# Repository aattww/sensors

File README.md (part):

# Summary

This project consists of simple Atmel ATmega328P based nodes utilizing HopeRF LoRa RFM95W/RFM96W radios. Battery-powered nodes measure temperature, humidity and barometric pressure, depending on connected hardware. Externally powered pulse type nodes count pulses from different utility meters and also connect to Kamstrup Multical energy meters. Gateway receives and collects these measurements from the sensor nodes and can be accessed by serial communication using Modbus RTU protocol via either two-wire RS-485 or common 3.3 volt UART. This enables interfacing with many DIY home automation systems such as [Domoticz](https://www.domoticz.com/), [Home Assistant](https://www.home-assistant.io/) and [openHAB](https://www.openhab.org/). Sensors uses custom circuit boards but is programmed with Arduino IDE.

This project is a complete package: it includes both hardware designs and software. *Schematics* contains PCB designs so you can manufacture or order PCBs from a factory and solder the nodes. Software is ready to be uploaded as it is. If you do not want to use the hardware designs provided, you should be able to use, for example, Arduino Pro Minis with protoboards instead. Browse through the .inos and the schematics to find out pin definitions. Remember to take into account battery usage if using Pro Minis or other "full size" Arduinos. Also remember that the components used are mostly 3.3 volt tolerant only, so using a 5 volt Uno requires level shifting.

Skip directly to [Instructions](#instructions), although I strongly recommend reading the whole readme first.

# Table of Contents

* [External requirements](#external-requirements)
  * [Libraries](#libraries)
  * [Hardware package (core)](#hardware-package-core)
* [Gateway](#gateway)
  * [Modbus registers](#modbus-registers)
    * [Gateway specific registers](#gateway-specific-registers)
    * [Battery powered node specific registers](#battery-powered-node-specific-registers)
    * [Pulse node specific registers](#pulse-node-specific-registers)
    * [Pulse node with Kamstrup Multical 602 energy meter specific registers](#pulse-node-with-kamstrup-multical-602-energy-meter-specific-registers)
* [Node types](#node-types)
  * [Battery](#battery)
    * [Supported sensors](#supported-sensors)
  * [Pulse](#pulse)
  * [Pulse with Kamstrup Multical 602 energy meter](#pulse-with-kamstrup-multical-602-energy-meter)
* [Radios](#radios)
* [Schematics and PCB](#schematics-and-pcb)
  * [BOM](#bom)
    * [Gateway / Pulse / Pulse with Kamstrup Multical](#gateway--pulse--pulse-with-kamstrup-multical)
    * [Battery](#battery-1)
  * [LEDs](#leds)
    * [Gateway](#gateway-1)
    * [Battery](#battery-2)
    * [Pulse / Pulse with Kamstrup Multical](#pulse--pulse-with-kamstrup-multical)
  * [Headers, terminals and buttons](#headers-terminals-and-buttons)
    * [Gateway](#gateway-2)
    * [Battery](#battery-3)
    * [Pulse / Pulse with Kamstrup Multical](#pulse--pulse-with-kamstrup-multical-1)
* [Instructions](#instructions)
* [Version history](#version-history)

# External requirements

Sensors requires a few external components to work: libraries provide functions for radio communications and connected sensors while hardware package handles needed fuses to work with custom boards used by Sensors. Follow carefully especially the instructions regarding RadioHead and Cryptography libraries, as these require a couple of underlying changes.

## Libraries

**RadioHead Packet Radio library for embedded microprocessors** provides support for RFM95W/RFM96W radios (and many others as well). Download from [airspayce.com](https://www.airspayce.com/mikem/arduino/RadioHead/). After extracting the library to your Arduino IDE libraries folder you will have to do one adjustment. In the beginning of *RadioHead/RH_RF95.h* change line  
`#define RH_RF95_FIFO_SIZE 255`  
to  
`#define RH_RF95_FIFO_SIZE 64`  
Communication will not work without this change. You also risk running out of SRAM without this adjustment.

**Arduino Cryptography Library** includes support for encryption. If you do not plan to encrypt traffic, you will not need this library. Download from [github.com](https://github.com/rweather/arduinolibs). You will need to download the ZIP and extract contents of *libraries* to your Arduino IDE libraries folder. Also remember to uncomment the following line at the very end of *RadioHead/RadioHead.h* to enable encryption:  
`//#define RH_ENABLE_ENCRYPTION_MODULE`  
You will also need to disable watchdog entropy harvesting by commenting out the following line at the beginning of *Crypto/RNG.cpp* because watchdog timer is already used by battery powered nodes:  
`#define RNG_WATCHDOG 1      // Harvest entropy from watchdog jitter.`  
If you are overwhelmed by all this, you may just want not to enable encryption at all. After all, Sensors is not exactly high security system anyway.

**LowPowerLab SI7021** library is needed to work with Silicon Labs Si7021 temperature and humidity sensor. Download from [github.com](https://github.com/LowPowerLab/SI7021).

**SparkFun BME280 Arduino Library** interfaces with Bosch Sensortech BME280 temperature, humidity and barometric pressure sensor. Documentation at [github.com](https://github.com/sparkfun/SparkFun_BME280_Arduino_Library). Install using Arduino IDE Library Manager.

## Hardware package (core)

Sensors uses a bit different hardware design than regular Arduino boards. For example, battery operated nodes run on internal 1 MHz clock and gateway uses external 8 MHz crystal. They also lack bootloader (although you could use it, hardware just doesn't provide serial pins to burn new firmware using bootloader anyway). Instead, program is flashed using ICSP through ISP header.

You could set the necessary fuses manually but it is considerably easier to just use a ready-made hardware package. MCUdude has a nice core specifically to do this. Download MCUdude's MiniCore from [github.com](https://github.com/MCUdude/MiniCore).

# Gateway

Gateway collects data from nodes and acts as an relay to a [Modbus](https://en.wikipedia.org/wiki/Modbus) network. By using Maxim Integrated MAX3485 RS-485 transceiver gateway can be connected to an existing RS-485 Modbus RTU network as a slave. Omitting the transceiver provides a direct TTL serial port. This can be accessed with, for example, another Arduino board, FTDI chip or connected directly to a Raspberry Pi. Regardless of the physical connection, gateway is accessed using Modbus protocol. Gateway requires regulated 3.3 volts or (unregulated) 5-12 volts DC power supply. In addition, gateway has three pulse inputs (pulse values are periodically saved to EEPROM and restored on power-up), one of which can be used as an NTC thermistor input. These inputs are also accessible via Modbus.

One drawback of Modbus protocol is that a slave can not inform the master of new messages. For this, pulse 2 can be enabled to work as an external interrupt. This pin behaves like an emulated open collector output (external high state voltage is limited to 3.3 volts, however). The pin will be pulled to ground when a message is received either from an *important* node or any node, depending on the gateway settings. After Modbus read has been done, this pin will be set back to high impedance state.

**Warning:** UART serial port is 3.3 volts, so don't connect it to a 5 volt system.

Why Modbus? Modbus is an easy to use and integrate protocol for this kind of data transfer. Although it is old and somewhat limited in features, it still provides all the necessary things and is widely used in industry. Libraries to access it exist for more or less every platform. Also, most DIY home automation systems ([Home Assistant](https://www.home-assistant.io/), [Domoticz](https://www.domoticz.com/) and [openHAB](https://www.openhab.org/) to name a few) have Modbus support.

## Modbus registers

Registers can be accessed using either function code 3 (read holding registers) or 4 (read input registers). Both return the same register values. Note that registers not defined can not be read. For example, trying to read registers 21-99 or 108-199 will return *illegal data address exception*.

### Gateway specific registers

| Address | Number | Name | Type / Unit | Notes |
| ------- | ------ | ---- | ---- | ----- |
| 0       | 30001  | Modbus errors (CRC failed or corrupted) | Counter |  |
| 1       | 30002  | Modbus overflown frames | Counter |  |
| 2       | 30003  | Modbus illegal function reads | Counter |  |
| 3       | 30004  | Modbus illegal address reads | Counter |  |
| 4       | 30005 | Modbus frames received | Counter |  |
| 5       | 30006  | Modbus frames sent | Counter |  |
| 6       | 30007  | Nodes during last hour | Counter |  |
| 7       | 30008  | Nodes during last 12 hours | Counter |  |
| 8       | 30009  | Nodes during last 24 hours | Counter |  |
| 9       | 30010  | At least one node low on battery | Boolean |  |
| 10       | 30011  | Gateway out of memory | Boolean |  |
| 11       | 30012  | Gateway uptime | Hour | |
| 12       | 30013  | Firmware version | | 8 MSB = major, 8 LSB = minor |
| 13       | 30014  | Status |  | See below for bits. |
| 14       | 30015  | Pulse 1 | Counter | 32 bit |
| 16       | 30017  | Pulse 2 | Counter | 32 bit |
| 18       | 30019  | Pulse 3 / Temperature | Counter / °C | 32 bit |
| 20       | 30021  | Last received node ID |  |  |

Status register bits (from LSB to MSB):
* Bit 0 **External SRAM:** *1* if gateway has external SRAM, *0* if using internal SRAM. Affects maximum number of nodes, see notes in [Schematics and PCB](#schematics-and-pcb).
* Bit 1-15 **Reserved**

### Battery powered node specific registers

First address is *node id * 100*. For example, this table shows addresses for a node id 1. Similarly, measurements for node id 2 start at address 200, and so on.

| Address | Number | Name | Type / Unit | Notes |
| ------- | ------ | ---- | ---- | ----- |
| 100       | 30101  | Last received | Minute | When was node last seen. |
| 101       | 30102  | Battery voltage | mV | Current battery voltage. |
| 102       | 30103  | Transmit power | % | Relative transmit power. |
| 103       | 30104  | Transmit interval | Minute | How often the node transmits at least. |
| 104       | 30105  | Header |  | Only 8 LSB, debug data. See below for bits. |
| 105       | 30106  | Temperature | °C | ×10 |
| 106       | 30107  | Relative humidity | RH% | ×10. **Only if node has Si7021 or BME280.** |
| 107       | 30108  | Barometric pressure / Temperature | hPa / °C | ×10. **Pressure if node has BME280, temperature if node has both Si7021 and NTC.** |

Header register bits (from LSB to MSB):
* Bit 0-2 **Node type:** Internal definiton of the node type.
* Bit 3 **Reserved**
* Bit 4 **Battery-powered:** *1* if node is battery-powered, *0* if powered externally.
* Bit 5 **Important:** *1* if node has declared itself important, *0* if not.
* Bit 6-7 **Reserved**

### Pulse node specific registers

First address is *node id * 100*. For example, this table shows addresses for a node id 2. Similarly, measurements for node id 3 start at address 300, and so on.

| Address | Number | Name | Type / Unit | Notes |
| ------- | ------ | ---- | ---- | ----- |
| 200       | 30201  | Last received | Minute | When was node last seen. |
| 201       | 30202  | Transmit power | % | Relative transmit power. |
| 202       | 30203  | Transmit interval | Minute | How often the node transmits at least. |
| 203       | 30204  | Header |  | Only 8 LSB, debug data. See below for bits. |
| 204       | 30205  | Pulse 1 | Counter | 32 bit |
| 206       | 30207  | Pulse 2 | Counter | 32 bit |
| 208       | 30209  | Pulse 3 / Temperature | Counter / °C | 32 bit |

Header register bits (from LSB to MSB):
* Bit 0-2 **Node type:** Internal definiton of the node type.
* Bit 3 **Reserved**
* Bit 4 **Battery-powered:** *1* if node is battery-powered, *0* if powered externally.
* Bit 5 **Important:** *1* if node has declared itself important, *0* if not.
* Bit 6-7 **Reserved**

### Pulse node with Kamstrup Multical 602 energy meter specific registers

First address is *node id * 100*. For example, this table shows addresses for a node id 3. Similarly, measurements for node id 4 start at address 400, and so on.

| Address | Number | Name | Type / Unit | Notes |
| ------- | ------ | ---- | ---- | ----- |
| 300       | 30301  | Last received | Minute | When was node last seen. |
| 301       | 30302  | Transmit power | % | Relative transmit power. |
| 302       | 30303  | Transmit interval | Minute | How often the node transmits at least. |
| 303       | 30304  | Header |  | Only 8 LSB, debug data. See below for bits. |
| 304       | 30305  | Pulse 1 | Counter | 32 bit |
| 306       | 30307  | Pulse 2 | Counter | 32 bit |
| 308       | 30309  | Pulse 3 / Temperature | Counter / °C | 32 bit |
| 310       | 30311  | Heat energy | kWh | 32 bit |
| 312       | 30313  | Actual flow | l/h | 32 bit |
| 314       | 30315  | Volume | m³ | ×100. 32 bit |
| 316       | 30317  | Actual power | kW | ×10. 32 bit |
| 318       | 30319  | Actual t₁ | °C | ×100. 32 bit |
| 320       | 30321  | Actual t₂ | °C | ×100. 32 bit |

Header register bits (from LSB to MSB):
* Bit 0-2 **Node type:** Internal definiton of the node type.
* Bit 3 **Reserved**
* Bit 4 **Battery-powered:** *1* if node is battery-powered, *0* if powered externally.
* Bit 5 **Important:** *1* if node has declared itself important, *0* if not.
* Bit 6-7 **Reserved**

# Node types

Sensors includes two main types of nodes: battery and pulse. Battery-powered low-power nodes monitor temperature, humidity and pressure. Pulse type nodes are externally powered and count pulses from utility meters. Pulse nodes also support connecting one NTC thermistor for temperature monitoring and RS-485 Modbus RTU. The latter enables the node to be connected to a Kamstrup Multical 602 energy meter.

## Battery

Battery powered sensors provide simple nodes to monitor temperature, humidity and barometric pressure. These nodes operate on two normal 1.5 volt AA alkaline batteries. If longer lifetime is needed or if node is placed in cold environment, more expensive 1.5 volt AA-size lithium batteries can also be used.

**Warning:** Hardware provides no reverse voltage protection in order to conserve power and to keep number of parts minimal, so **make sure to observe polarity when inserting batteries or you will destroy the node**.

Nodes spend most of the time sleeping, only to wake up to take measurements and send values to gateway. Frequency can be controlled through settings at the beginning of the code file. In threshold mode, nodes wake up periodically and take measurements. If values differ enough from previously sent ones, a message is sent. If not, nodes return to sleep. However, there is a specific force time controlling how often a new message is sent at least regardless of threshold. If a node is not operating in threshold mode, it will send a message every time it wakes up.

### Supported sensors

Nodes support three types of sensors: Silicon Labs Si7021, Bosch Sensortech BME280, and a common NTC thermistor. The first one has temperature and humidity, the second one adds barometric pressure, and the latter provides only temperature. A node can have only one kind of sensor, or as a special case both Si7021 and NTC at the same time. PCB provides footprints for all, and the exact type is defined in runtime. That is, every node is flashed with the same software and it checks at bootup what kind of sensor configuration is connected.

**Si7021** sensors can be bought as breakout boards from eBay and similar places for a couple of dollars. When buying the sensor, get one that does not include voltage regulator and I2C level shifting. Battery powered nodes operate on 3.3 volts so Si7021 can be fed directly. Not having (unnecessary) regulator saves battery power. For example, [this one](https://www.ebay.com/itm/SMD-MINI-Si7021-Temperature-and-Humidity-Sensor-I2C-Interface-for-Arduino/264394330907) is recommended, while [this one](https://www.ebay.com/itm/Si7021-Industrial-High-Precision-Humidity-Sensor-I2C-Interface-for-Arduino/201539848414) is not.

**BME280** sensors are also available in eBay, Aliexpress and similar as breakout boards. They are a bit more expensive. These seem not to be available without the onboard regulator, so if you want to lower power consumption, your only option is to remove the regulator. Example image of a removed regulator [shown here](images/bme280.jpg). [This sensor](https://www.ebay.com/itm/Breakout-Temperature-Humidity-Barometric-Pressure-BME280-Digital-Sensor-Module/401000227934), for example, has been used successfully.

**Note:** Chinese sellers sometimes mix the BME280 with earlier and less featured BMP280. Be careful when buying the sensor. Info about this for example [here](https://goughlui.com/2018/08/05/note-bosch-sensortec-bmp280-vs-bme280-sensor-confusion/) and [here](https://www.meteocercal.info/forum/Thread-Bosch-Sensortec-BMP280-vs-BME280-Sensor-Confusion).

**NTC thermistors** can be purchased from the same places as the other sensors. When buying thermistors, make sure you get three necessary values: *nominal resistance*, *nominal temperature* and *beta coefficient*. For example, [this thermistor](https://www.ebay.com/itm/5PCS-1m-NTC-Thermistor-accuracy-temperature-sensor-10K-1-3950-Waterproof-Probe/311572298670) has been successfully used and works with the default values.

## Pulse

Pulse type nodes are intended to measure pulses from a water, electricity, gas or other kind of meter with pulse output. Nodes have three pulse inputs, one of which can be used as an NTC thermistor input instead of a pulse input. Pulse inputs are pulled high internally by microcontroller or with optional external resistors, and connected meter pulls it low to ground. Pulse values are periodically saved to EEPROM and restored on power-up. Pulse nodes require either regulated 3.3 volts or (unregulated) 5-12 volts DC power supply. They use the same PCB as the gateway.

## Pulse with Kamstrup Multical 602 energy meter

These nodes are regular pulse nodes with added support for Kamstrup Multical 602 energy meter. Node is connected by RS-485 to a Multical 602 energy meter and periodically reads certain values from the meter. See Modbus register listing above for these values.

**Note:** Multical 602 seems to be discontinued and replaced by Multical 603. According to datasheet, Multical 603 supports the same Modbus registers as the old 602. Therefore nodes should work with newer 603s but this is untested.

**Protip:** Using this node as an example, it should be quite easy to connect some other kind of Modbus RTU capable device to a Pulse type node and adjust code accordingly. This way you can read any other Modbus meters or devices via Sensors nodes.

# Radios

Sensors utilize HopeRF RFM95W and RFM96W LoRa radios. RFM95W is for 868/915 MHz and RFM96W for 433 MHz. These are cheap low power radios with very good range. Battery nodes use wire or helical antennas, while gateway and pulse nodes have SMA connectors for better performing antennas. Please consider local regulations when choosing frequency range, bandwidth, transmit power and other radio related settings. Nodes automatically adjust transmit power to the lowest possible level.

Attainable range depends greatly on numerous things but personally I have easily achieved over one kilometer through a reinforced concrete wall and a metal facade. This was between a gateway with a dipole SMA antenna and a battery node with helical antenna. The same setup also reached over 200 meters through buildings in a more built environment. However, as with wireless communication in general, your results will vary.

**Note:** On the PCB there is footprint for older HopeRF RFM69HW radio as well. It should work, but it has not been tested and there is currently no support in software for this. Feel free to create a new branch and implement it.

# Schematics and PCB

Following is the table of bill of materials. Not all components are needed, see the notes below for these parts. Majority of the SMD components are 1206 package for easier hand soldering. Gateways and pulse nodes share the same PCB.

Some notes:
* MAX3485 transceiver is needed only if you connect the gateway to an existing RS-485 network. If you use direct UART it is not needed. In this case, remember to also short *COMM_JMP* at the bottom.
* External pull-up resistors are probably not needed in most cases as internal ones in ATmega328P are usually adequate. However, if you are connecting NTC thermistor to pulse 3, remember to solder the 10 kOhm series resistor.
* Pulse smoothing capacitors are optional. Use them if you encounter erroneous pulses, ie. too many pulses are counted. For example, I had a [rain gauge](https://www.amazon.co.uk/dp/B00QDMBXUA) connected to a pulse input with a rather long cable (about 10 meters running next to mains power supply for part of length). Extra pulses were counted even when no rain had fallen. Adding a 10 uF capacitor removed these wrong measures.
* MIC5209 regulator makes it possible to power the gateway/pulse node with DC voltage between 5-12 volts (technically up to 16 volts but it might start to get warm). If you can supply the board with regulated 3.3 volts, you can omit the regulator. In this case, also short the *PWR_JMP*.
* The Microchip 23K256 SRAM chip is optional. Without it, gateway falls back using its internal SRAM. However, this severely limits the amount of nodes. With the 23K256 gateway supports 100 nodes regardless of type, without it only 10. This varies by node type, however. For example, without external SRAM gateway supports 10 battery nodes, or 5 pulse nodes, or 6 battery nodes plus 2 pulse nodes.
* SMA connector can be omitted and replaced with a wire or a helical antenna if these smaller gain antennas are sufficient. You can also, with some very careful alignment, solder a u.FL connector on to the SMA connector footprint. This allows using a u.FL to SMA pigtail to move the actual SMA connector away.

I have successfully ordered PCBs from Seeed Studio. You can get boards for 10 gateways/pulse nodes and 10 battery nodes for $9.80 plus postage. Of course any prototype PCB factory will work. PCBs are designed not to have any tight spacings or need for strict tolerances. For gateway and pulse node, select 1.6mm thickness (the enclosure will hold the PCB better). With battery nodes, boards can be thinner (for example 1.2mm works well). Other options should be okay with defaults.

Boards are designed to fit the enclosures mentioned in the table. [Bud Industries DMB-4771](https://www.budind.com/view/Plastic+Boxes/DIN+Rail+Mount+Multi-Board+Box) is a 35mm DIN rail mounted box, while [Supertronic PP42](http://www.supertronic.com/en/cajas_de_plastico/sensors/29/pp42/50) is a simple wall mounted enclosure (use double-sided tape). In the *schematics* folder there is also *AP9_holder.stl* which is a 3D model of a simple holder to fix a battery node into an [ABB AP9 junction box](https://new.abb.com/products/2TKA140012G1/ap9-junction-box-ip65). This is especially handy if you install a node outside and have access to a 3D printer. You will need two holders and a set of small screws. You will also need to have a way to make the box rain-proof but still let humidity and temperature in. Poking some holes into membrane cable entries is one way, or if you want to go professional, use a sintered protective cover. [This](https://www.ebay.com/itm/Protective-Cover-SHT10-SHT20-Soil-Temperature-Humidity-Moisture-Sensor-Shell/173940209491) has been proven to work: a BME280 breakout board will *just* fit inside if you solder wires to the board as [shown here](images/bme280.jpg). Remember to wrap the breakout board (but not the sensor itself) with some insulating tape or use heat shrink to prevent short circuits. [This image](images/si7021_wired.jpg) shows an Si7021 breakout board prepared for outdoor sensor use. You will also need to drill off the plastic inside with the connectors of the protective cover. Use some imagination here. A ready-made weatherproofed sensor looks something like [this](images/weatherproof_node.jpg). Connecting an NTC thermistor with sufficiently long wire will make a nice water temperature node as shown [here](images/water_temperature_node.jpg).

## BOM

### Gateway / Pulse / Pulse with Kamstrup Multical

| Part | Value | Device | Package | Type | Notes |
| ---- | ----- | ------ | ------- | ---- | ----- |
| C1 | 100 nF | Decoupling capacitor | 1206 | Ceramic | |
| C2 | 22 pF | Crystal capacitor | 1206 | Ceramic | |
| C3 | 22 pF | Crystal capacitor | 1206 | Ceramic | |
| C4 | 100 nF | Decoupling capacitor | 1206 | Ceramic | Used only with RFM95W / RFM96W. |
| C5 | 100 nF | Decoupling capacitor | 1206 | Ceramic | Used only with RFM69HW. |
| C6 | 100 nF | Decoupling capacitor | 1206 | Ceramic | Used only with U2 (MAX3485). |
| C7 | 1 uF | Power input capacitor | 1206 | Tantalum | |
| C8 | 1 uF | Power output capacitor | 1206 | Tantalum | |
| C9 | 10 uF | Power output capacitor | 1206 | Ceramic | |
| C10 | 100 nF | Decoupling capacitor | 1206 | Ceramic | Used only with 23K256. |
| C11 | Depends | Pulse 3 smoothing capacitor | 1206 | Ceramic | Use if erroneous pulses are counted. |
| C12 | Depends | Pulse 2 smoothing capacitor | 1206 | Ceramic | Use if erroneous pulses are counted. |
| C13 | Depends | Pulse 1 smoothing capacitor | 1206 | Ceramic | Use if erroneous pulses are counted. |
| R1 | 10 kOhm | Reset pull-up resistor | 1206 | | |
| R2 | 10 kOhm | Radio slave select pull-up resistor | 1206 | | |
| R3 | 120 Ohm | RS-485 termination resistor | 1206 | | Used only with U2 (MAX3485). |
| R4 | Depends | Power LED resistor | 1206 | | Select value based on LED in use. |
| R5 | Depends | Activity LED resistor | 1206 | | Select value based on LED in use. |
| R6 | Depends | Serial activity LED resistor | 1206 | | Select value based on LED in use. |
| R7 | Depends / 10 kOhm | Pulse 3 pull-up / NTC series resistor | 1206 | | Use if ATmega328P internal pull-up resistor is not strong enough, or NTC is to be used. |
| R8 | Depends | Pulse 2 pull-up resistor | 1206 | | Use if ATmega328P internal pull-up resistor is not strong enough. |
| R9 | Depends | Pulse 1 pull-up resistor | 1206 | | Use if ATmega328P internal pull-up resistor is not strong enough. |
| R10 | 10 kOhm | SRAM slave select pull-up resistor | 1206 | | Used only with 23K256. |
| D1 | | Serial activity LED | 1206 | | |
| D2 | | Power LED | 1206 | | |
| D3 | | Activity LED | 1206 | | |
| Y1 | 8 MHz | HC-49US 8 MHz crystal | | | |
| S1 | | Momentary push button | 3x6 mm | | For example, [this one](https://www.ebay.com/itm/100-Pcs-3x6x2-5mm-Momentary-Tact-SMD-SMT-Push-Button-Micro-Switch-2-Pin/272961316148). |
| X1 | | SMA connector | | | For example, [this one](https://www.ebay.com/itm/End-Launch-PCB-Mount-SMA-Female-Plug-Straight-RF-Connector-Adapter-10-Pcs-R7Z6-/253508669169). |
| Header | | ISP programming header | 2x3, 0.1" pitch | | |
| Header | | Node ID selection header | 2x5, 0.1" pitch | | |
| Header | | RS-485 terminate and J1 header | 2x2, 0.1" pitch | | |
| Screw terminals | | Power, serial, pulse grounds, pulse inputs | 3x2 + 1x3, 5.08mm pitch | | For example, [two terminal](https://www.ebay.com/itm/20PCS-KF301-2P-2-Pin-Plug-in-Terminal-Block-Connector-5-08mm-Pitch-Through-Hole/381374540897) and [three terminal](https://www.ebay.com/itm/10pcs-KF301-3P-5-08mm-Blue-Connect-Terminal-Blue-Screw-Terminal-Connector/201415082308). |
| PWR_JMP | | Solder jumper | 1206 | | Short or use a zero-ohm resistor if not using U4, i.e. board is provided external regulated 3.3 volts. |
| COMM_JMP | | Solder jumper | | | Short if not using U2, i.e. direct UART is used. |
| U1 | | Atmel ATmega328P microcontroller | DIP-28 | | Preferably use a socket. |
| U2 | | Maxim MAX3485 RS-485 transceiver | DIP-8 | | Preferably use a socket. Use only if connected to an RS-485 network. |
| U3 | | HopeRF RFM95W/RFM96W/RFM69HW | | | |
| U4 | | Microchip MIC5209-3.3 regulator | SOT-223 | | Optional (see notes above). |
| U5 | | Microchip 23K256 SRAM | DIP-8 | | Optional (see notes above). Preferably use a socket. |
| Enclosure | | Bud Industries DMB-4771 | | | |

### Battery

| Part | Value | Device | Package | Type | Notes |
| ---- | ----- | ------ | ------- | ---- | ----- |
| C1 | 100 nF | Decoupling capacitor | 1206 | Ceramic | |
| C2 | 100 nF | Decoupling capacitor | 1206 | Ceramic | Used only with RFM69HW. |
| C3 | 100 nF | Decoupling capacitor | 1206 | Ceramic | Used only with RFM95W / RFM96W. |
| C4 | 100 nF | Power smoothing capacitor | 1206 | Ceramic | |
| C5 | 10 uF | Power smoothing capacitor | 1206 | Ceramic | |
| C6 | 100 nF | Decoupling capacitor | 1206 | Ceramic | |
| R1 | Depends | Activity LED resistor | 1206 | | Select value based on LED in use. |
| R2 | 10 kOhm | Reset pull-up resistor | 1206 | | |
| R3 | 10 kOhm | NTC series resistor | 1206 | | Use only with NTC. |
| R4 | 10 kOhm | Radio slave select pull-up resistor | 1206 | | |
| D1 | | Activity LED | 1206 | | |
| S1 | | Momentary push button | 3x6 mm | | For example, [this one](https://www.ebay.com/itm/100-Pcs-3x6x2-5mm-Momentary-Tact-SMD-SMT-Push-Button-Micro-Switch-2-Pin/272961316148). |
| Antenna | | Antenna for frequency in use, helical or wire | | | For example, [this one](https://www.ebay.com/itm/10PCS-868MHz-Helical-Antenna-2-15dBi-13mm-HPD215T-B-868MHZ-Stable-Remote-Contorl/311598709972). |
| Header | | ISP programming header | 2x3, 0.1" pitch | | |
| Header | | Node ID selection header | 2x6, 0.1" pitch | | |
| Header | | J1 header | 1x2, 0.1" pitch | | |
| U1 | | Atmel ATmega328P microcontroller | DIP-28 | | Preferably use a socket. |
| U2 / U3 | | Si7021 / BME280 sensor | | | Two footprints for different pin orders. See [Supported sensors](#supported-sensors) for more info. |
| U4 | | HopeRF RFM95W/RFM96W/RFM69HW | | | |
| NTC | | NTC thermistor | | | Header provided. See [Supported sensors](#supported-sensors) for more info. |
| Battery holder | | Holder for two AA size batteries | | | For example, a pair of [these](https://www.ebay.com/itm/AA-1-5V-PP3-Battery-or-Open-with-Switch-Holder-AA-x-1-Holder-PCB-Amount-5-C6T2-/283528370571). |
| Enclosure | | Supertronic PP42 | | | |

## LEDs

Boards have a few onboard LEDs to indicate different events. This chapter describes these events. All boards will blink the current running firmware version after power-up.

### Gateway

*PWR* is lit whenever gateway is powered. *L2* blinks when gateway is transmitting in Modbus network. The following table concerns *L1*.

| Blinks | Interval | Description | During | Notes |
| ------ | -------- | ----------- | ------ | ----- |
| 1 | 2 sec. | Illegal ID set. | Startup | Check ID headers and reboot. |
| 5 | 2 sec. | Failed to initialize radio. | Startup | Check connections. |
| 1 | - | Received and saved a message from a node. | Operation |  |
| 2 | - | Received a message from a node but memory is full. | Operation | Add external SRAM or lower amount of nodes. |
| 3 | - | Successful Modbus read from master. | Operation |  |
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
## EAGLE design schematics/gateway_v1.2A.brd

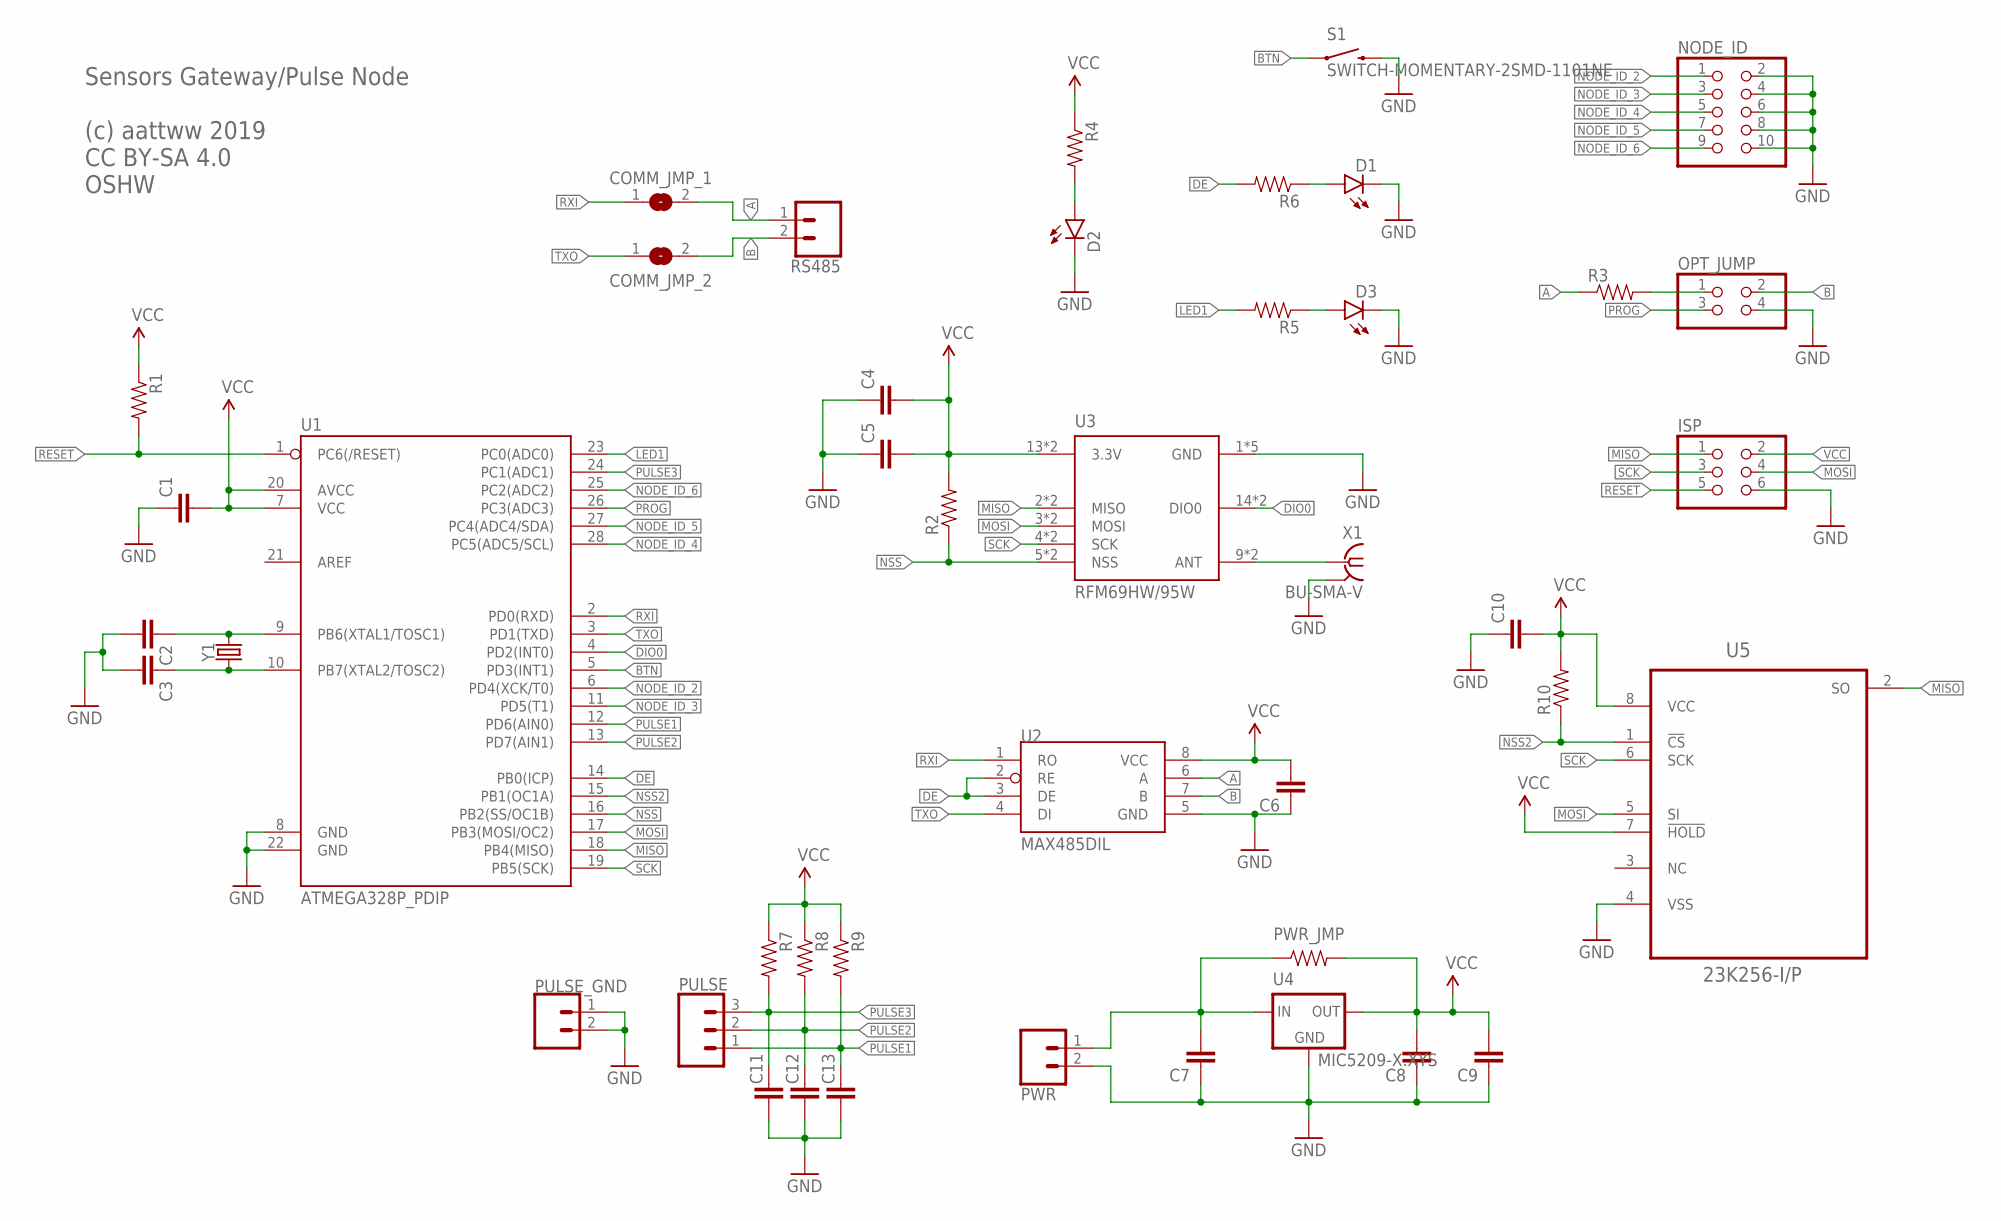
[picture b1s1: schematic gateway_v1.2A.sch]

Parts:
C1, C2, C3, C4, C5, C6, C7, C8, C9, C10, C11, C12, C13: CAP1206; 1206
COMM_JMP_1, COMM_JMP_2: SJ
D1, D2, D3: LED1206; LED-1206
ISP: PINHD-2X3; 2X03
NODE_ID: PINHD-2X5; 2X05
OPT_JUMP: PINHD-2X2; 2X02
PULSE: CONN_03-SCREW-5MM; SCREWTERMINAL-5MM-3
PULSE_GND: CONN_025MM; SCREWTERMINAL-5MM-2
PWR: CONN_025MM; SCREWTERMINAL-5MM-2
PWR_JMP: RESISTOR1206; 1206
R1, R2, R3, R4, R5, R6, R7, R8, R9, R10: RESISTOR1206; 1206
RS485: CONN_025MM; SCREWTERMINAL-5MM-2
S1: SWITCH-MOMENTARY-2SMD-1101NE; TACTILE-SWITCH-1101NE
U1: ATMEGA328P_PDIP; DIL28-3
U2: MAX485DIL; DIL08
U3: RFM69HW/95W
U4: MIC5209-X.XYS; SOT223
U5: 23K256-I/P; DIP254P762X533-8
X1: BU-SMA-V
Y1: CRYSTALPTH-HC49US; HC49US

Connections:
A: COMM_JMP_1.2, R3.1, RS485.1, U2.6 (A)
B: COMM_JMP_2.2, OPT_JUMP.2, RS485.2, U2.7 (B)
BTN: S1.1, U1.5 (PD3(INT1))
DE: R6.2, U1.14 (PB0(ICP)), U2.2 (RE), U2.3 (DE)
DIO0: U1.4 (PD2(INT0)), U3.14 (DIO0), U3.22 (DIO0)
GND: C1.1, C2.2, C3.2, C4.1, C5.1, C6.1, C7.1, C8.1, C9.1, C10.1, C11.2, C12.2, C13.2, D1.C, D2.C, D3.C, ISP.6, NODE_ID.2, NODE_ID.4, NODE_ID.6, NODE_ID.8, NODE_ID.10, OPT_JUMP.4, PULSE_GND.1, PULSE_GND.2, PWR.2, S1.2, U1.8 (GND), U1.22 (GND), U2.5 (GND), U3.1 (GND), U3.8 (GND), U3.10 (GND), U3.29 (GND), U3.31 (GND), U4.2 (GND), U4.4 (GND), U5.4 (VSS), X1.2, X1.3 (2), X1.4 (2), X1.5 (2)
LED1: R5.2, U1.23 (PC0(ADC0))
MISO: ISP.1, U1.18 (PB4(MISO)), U3.2 (MISO), U3.33 (MISO), U5.2 (SO)
MOSI: ISP.4, U1.17 (PB3(MOSI/OC2)), U3.3 (MOSI), U3.34 (MOSI), U5.5 (SI)
unnamed: U3.9 (ANT), U3.30 (ANT), X1.1
unnamed: OPT_JUMP.1, R3.2
unnamed: C2.1, U1.9 (PB6(XTAL1/TOSC1)), Y1.2
unnamed: C3.1, U1.10 (PB7(XTAL2/TOSC2)), Y1.1
unnamed: D2.A, R4.2
unnamed: D1.A, R6.1
unnamed: D3.A, R5.1
unnamed: C7.2, PWR.1, PWR_JMP.1, U4.1 (IN)
NODE_ID_2: NODE_ID.1, U1.6 (PD4(XCK/T0))
NODE_ID_3: NODE_ID.3, U1.11 (PD5(T1))
NODE_ID_4: NODE_ID.5, U1.28 (PC5(ADC5/SCL))
NODE_ID_5: NODE_ID.7, U1.27 (PC4(ADC4/SDA))
NODE_ID_6: NODE_ID.9, U1.25 (PC2(ADC2))
NSS: R2.1, U1.16 (PB2(SS/OC1B)), U3.5 (NSS), U3.35 (NSS)
NSS2: R10.1, U1.15 (PB1(OC1A)), U5.1 (!CS)
PROG: OPT_JUMP.3, U1.26 (PC3(ADC3))
PULSE1: C13.1, PULSE.1, R9.2, U1.12 (PD6(AIN0))
PULSE2: C12.1, PULSE.2, R8.2, U1.13 (PD7(AIN1))
PULSE3: C11.1, PULSE.3, R7.2, U1.24 (PC1(ADC1))
RESET: ISP.5, R1.2, U1.1 (PC6(/RESET))
RXI: COMM_JMP_1.1, U1.2 (PD0(RXD)), U2.1 (RO)
SCK: ISP.3, U1.19 (PB5(SCK)), U3.4 (SCK), U3.32 (SCK), U5.6 (SCK)
TXO: COMM_JMP_2.1, U1.3 (PD1(TXD)), U2.4 (DI)
VCC: C1.2, C4.2, C5.2, C6.2, C8.2, C9.2, C10.2, ISP.2, PWR_JMP.2, R1.1, R2.2, R4.1, R7.1, R8.1, R9.1, R10.2, U1.7 (VCC), U1.20 (AVCC), U2.8 (VCC), U3.13 (3.3V), U3.28 (3.3V), U4.3 (OUT), U5.7 (!HOLD!), U5.8 (VCC)

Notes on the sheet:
Sensors Gateway/Pulse Node (c) aattww 2019 CC BY-SA 4.0 OSHW

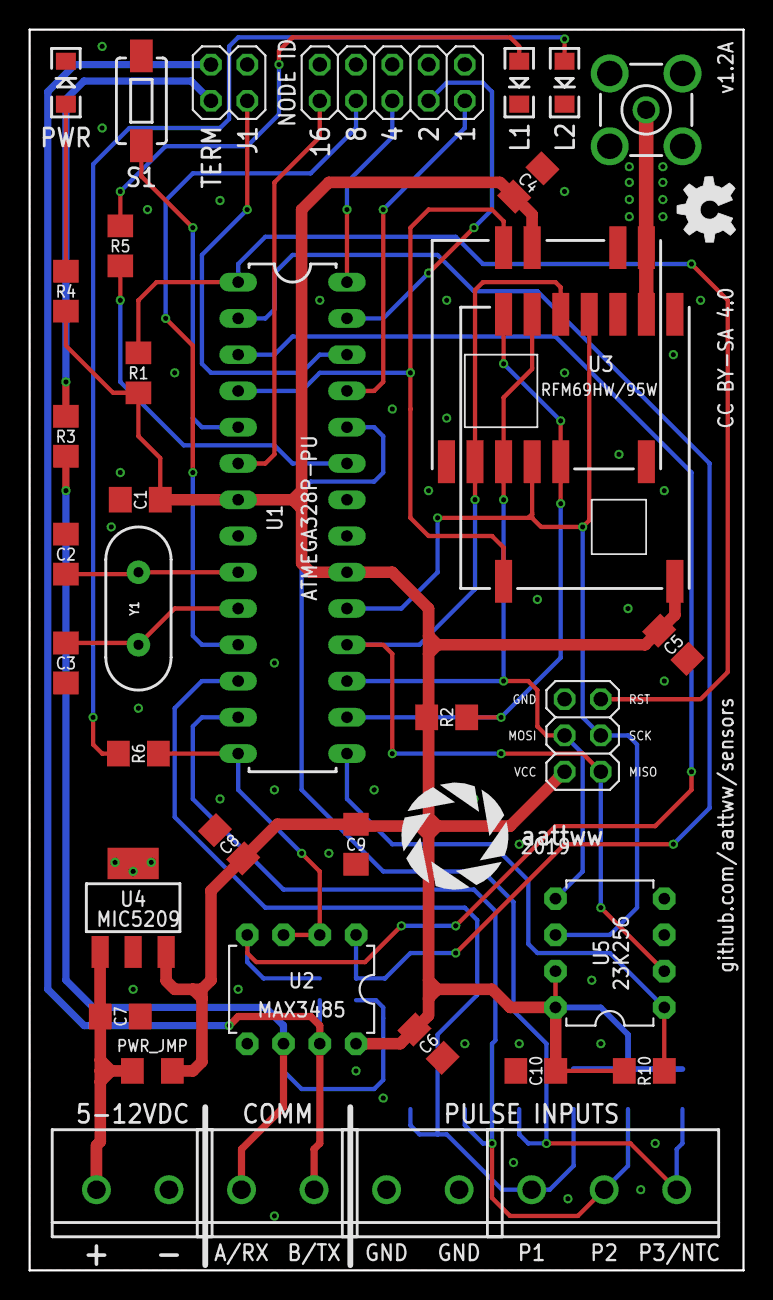
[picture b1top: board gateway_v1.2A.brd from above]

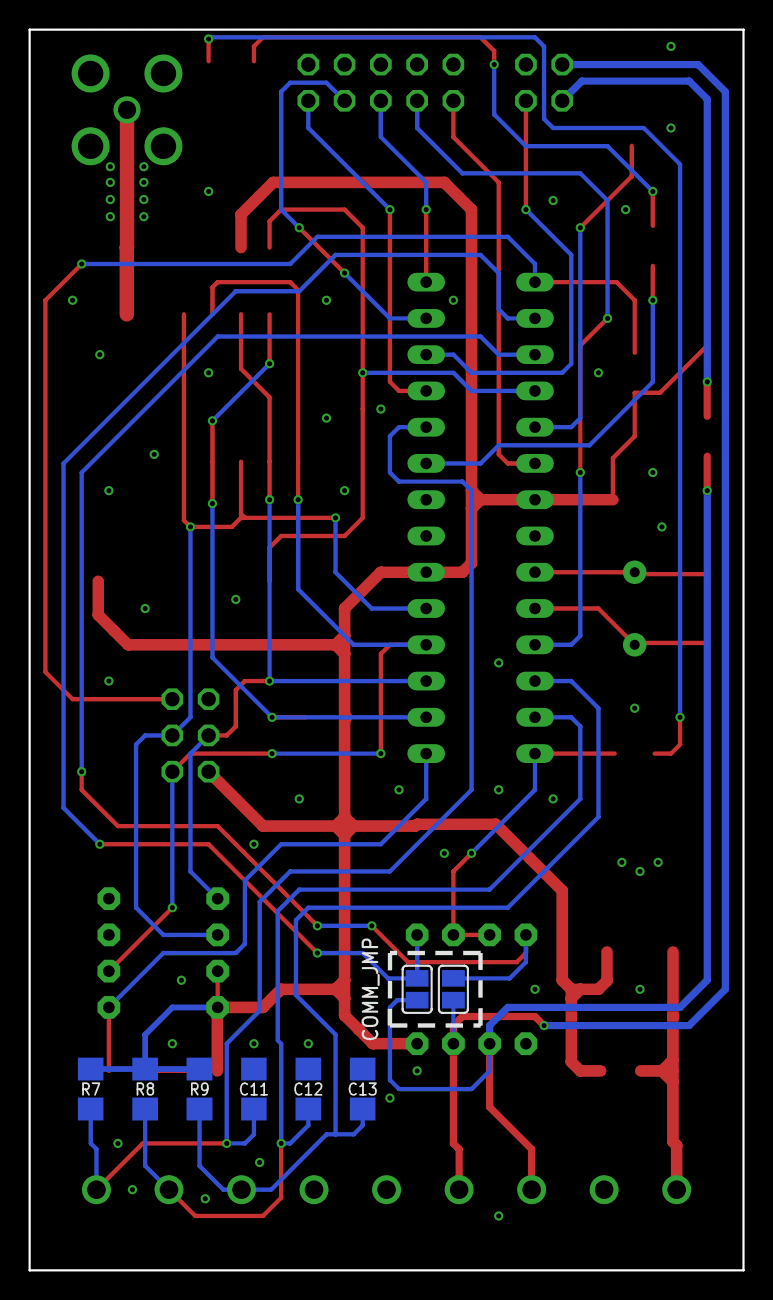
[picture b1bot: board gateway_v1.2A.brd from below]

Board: 2 copper layers, 50.0 x 86.9 mm, 46 parts (8 on the bottom side), 33 nets.

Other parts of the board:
U$1: OSHW_5MM
U$3: LOGO_7.5MM

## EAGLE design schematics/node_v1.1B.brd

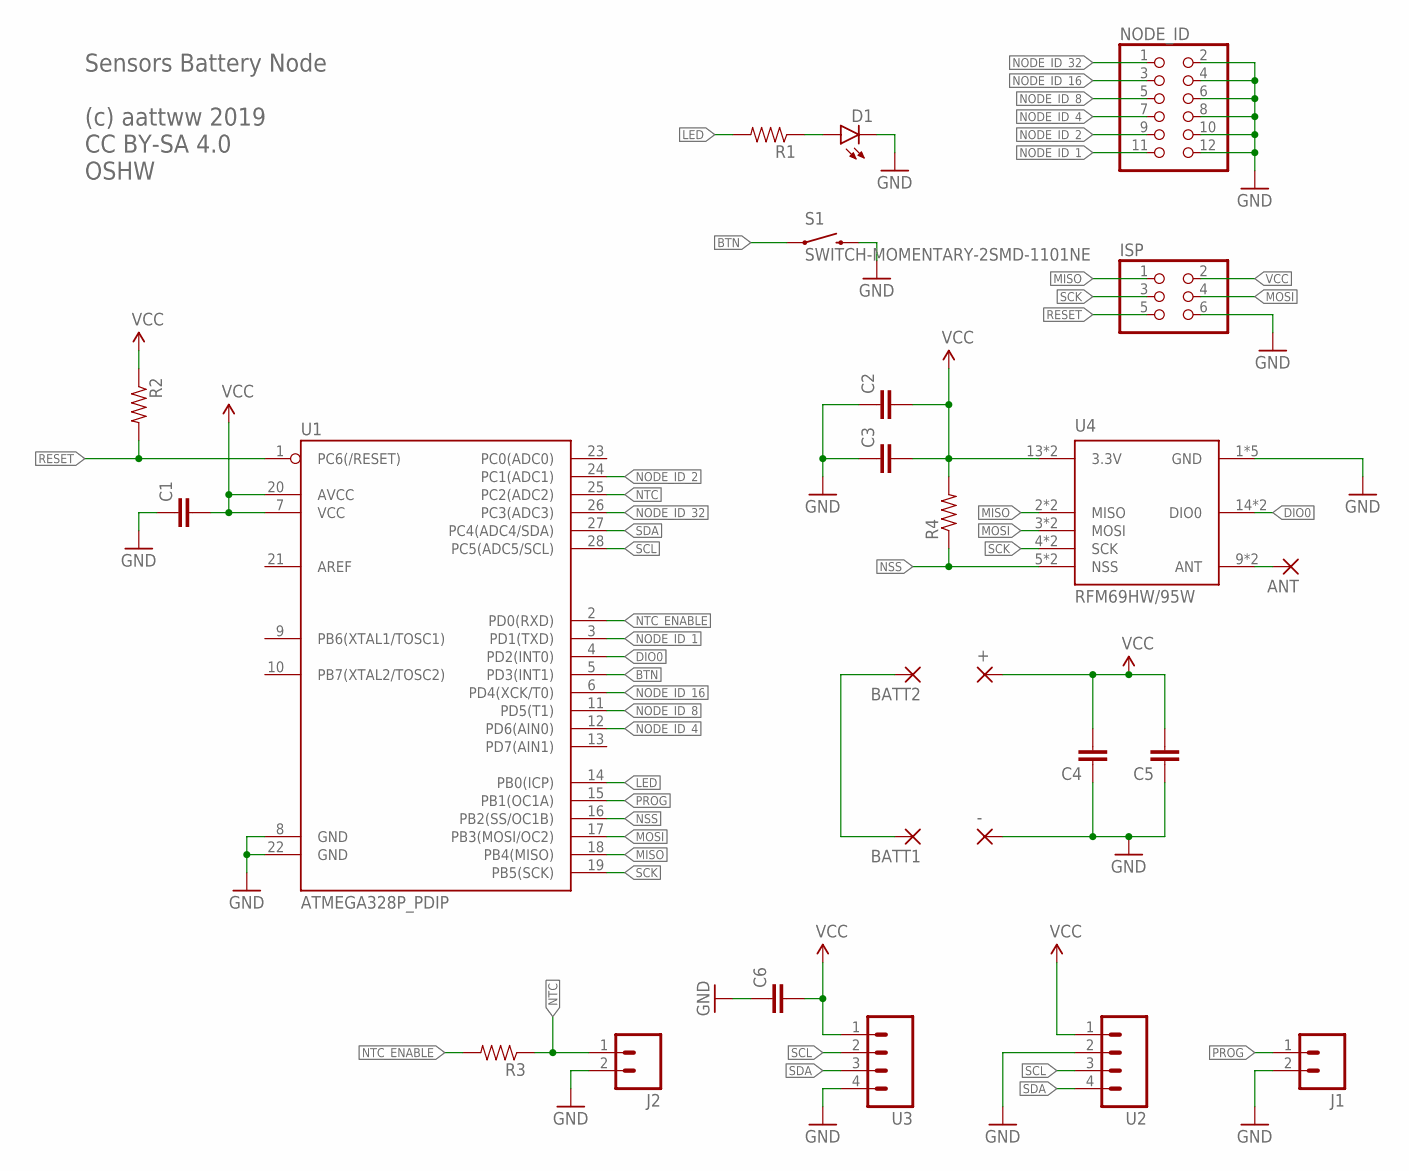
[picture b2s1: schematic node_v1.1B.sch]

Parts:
+: 2,15/1,0
-: 2,15/1,0
ANT: 2,15/1,0
BATT1, BATT2: 2,15/1,0
C1, C2, C3, C4, C5, C6: CAP1206; 1206
D1: LED1206; LED-1206
ISP: PINHD-2X3; 2X03
J1, J2: M02PTH; 1X02
NODE_ID: PINHD-2X6; 2X06
R1, R2, R3, R4: RESISTOR1206; 1206
S1: SWITCH-MOMENTARY-2SMD-1101NE; TACTILE-SWITCH-1101NE
U1: ATMEGA328P_PDIP; DIL28-3
U2, U3: M041X04_NO_SILK; 1X04_NO_SILK
U4: RFM69HW/95W

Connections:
BTN: S1.1, U1.5 (PD3(INT1))
DIO0: U1.4 (PD2(INT0)), U4.14 (DIO0), U4.22 (DIO0)
GND: -.1, C1.1, C2.1, C3.1, C4.1, C5.1, C6.1, D1.C, ISP.6, J1.2, J2.2, NODE_ID.2, NODE_ID.4, NODE_ID.6, NODE_ID.8, NODE_ID.10, NODE_ID.12, S1.2, U1.8 (GND), U1.22 (GND), U2.2, U3.4, U4.1 (GND), U4.8 (GND), U4.10 (GND), U4.29 (GND), U4.31 (GND)
LED: R1.2, U1.14 (PB0(ICP))
MISO: ISP.1, U1.18 (PB4(MISO)), U4.2 (MISO), U4.33 (MISO)
MOSI: ISP.4, U1.17 (PB3(MOSI/OC2)), U4.3 (MOSI), U4.34 (MOSI)
unnamed: ANT.1, U4.9 (ANT), U4.30 (ANT)
unnamed: BATT1.1, BATT2.1
unnamed: D1.A, R1.1
NODE_ID_1: NODE_ID.11, U1.3 (PD1(TXD))
NODE_ID_2: NODE_ID.9, U1.24 (PC1(ADC1))
NODE_ID_4: NODE_ID.7, U1.12 (PD6(AIN0))
NODE_ID_8: NODE_ID.5, U1.11 (PD5(T1))
NODE_ID_16: NODE_ID.3, U1.6 (PD4(XCK/T0))
NODE_ID_32: NODE_ID.1, U1.26 (PC3(ADC3))
NSS: R4.1, U1.16 (PB2(SS/OC1B)), U4.5 (NSS), U4.35 (NSS)
NTC: J2.1, R3.1, U1.25 (PC2(ADC2))
NTC_ENABLE: R3.2, U1.2 (PD0(RXD))
PROG: J1.1, U1.15 (PB1(OC1A))
RESET: ISP.5, R2.2, U1.1 (PC6(/RESET))
SCK: ISP.3, U1.19 (PB5(SCK)), U4.4 (SCK), U4.32 (SCK)
SCL: U1.28 (PC5(ADC5/SCL)), U2.3, U3.2
SDA: U1.27 (PC4(ADC4/SDA)), U2.4, U3.3
VCC: +.1, C1.2, C2.2, C3.2, C4.2, C5.2, C6.2, ISP.2, R2.1, R4.2, U1.7 (VCC), U1.20 (AVCC), U2.1, U3.1, U4.13 (3.3V), U4.28 (3.3V)

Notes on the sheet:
Sensors Battery Node (c) aattww 2019 CC BY-SA 4.0 OSHW

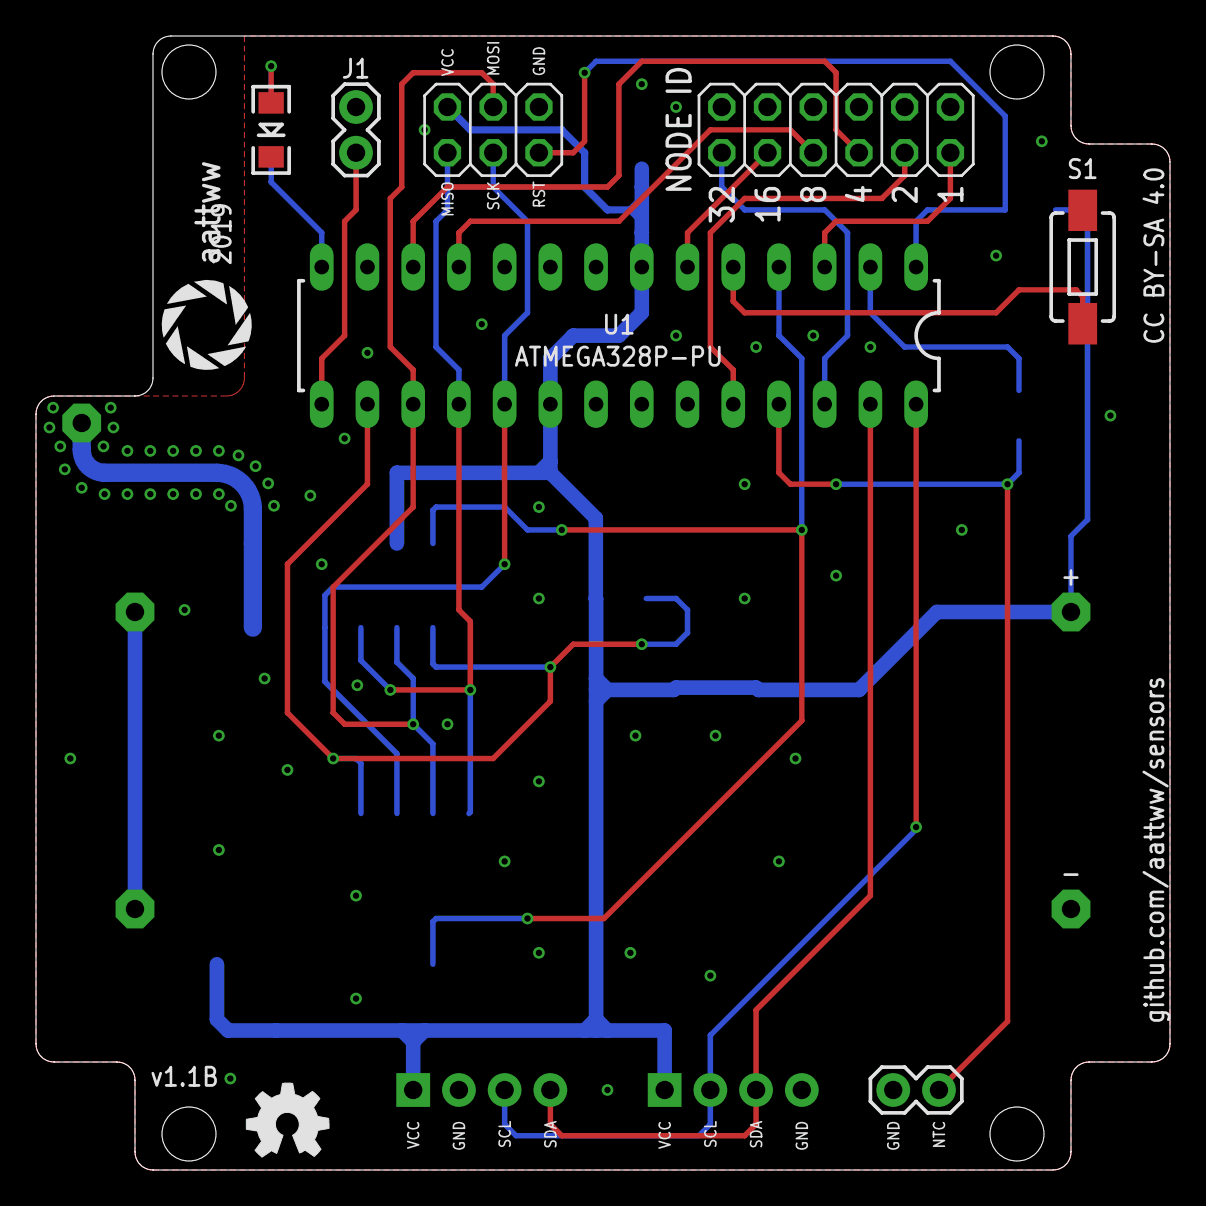
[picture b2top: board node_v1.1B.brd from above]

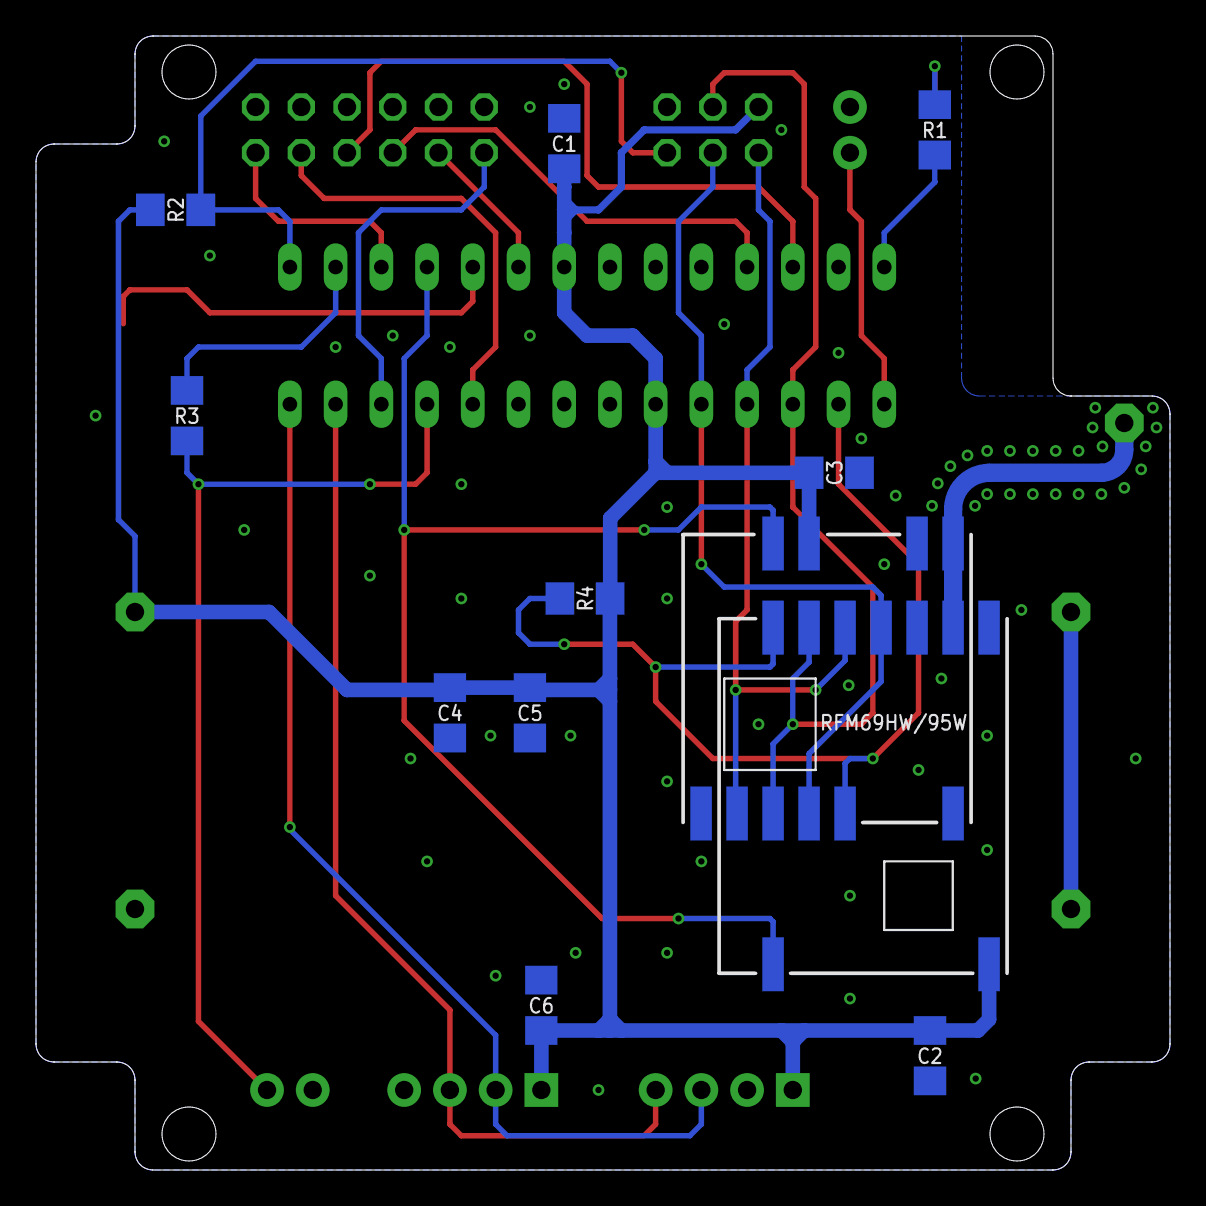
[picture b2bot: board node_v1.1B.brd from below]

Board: 2 copper layers, 63.0 x 63.0 mm, 27 parts (11 on the bottom side), 24 nets.

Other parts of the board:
U$1: OSHW_5MM
U$2: LOGO_5MM

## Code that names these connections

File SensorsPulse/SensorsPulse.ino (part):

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#endif

#define LED_PIN         A0
#define BTN_PIN         3
#define P1_PIN          6
#define P2_PIN          7
#define P3_PIN          A1
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uint8_t transmitPowerRaw = 25;
int8_t lastReportedRSSI;

volatile uint32_t pulse1 = 0;
volatile uint32_t pulse2 = 0;
volatile uint32_t pulse3 = 0;

#if defined NODE_TYPE_MULTICAL
uint32_t energy = 0;
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  pinMode(LED_PIN, OUTPUT);
  
  // Button
  pinMode(BTN_PIN, INPUT_PULLUP);
  
  // Jumper J1
  pinMode(JMP_PIN, INPUT_PULLUP);
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  delay(10);
  
  // Enter programming mode (currently does nothing) if button is pressed. Also set debug mode.
  if (!digitalRead(BTN_PIN)) {
    enterProgMode();
    isDebugMode = true;
  }
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  delay(2000);
  
  // If jumper is set and button pressed, clear pulse values from EEPROM.
  if (!digitalRead(JMP_PIN) && !digitalRead(BTN_PIN)) {
    clearPulsesFromEEPROM();
  }
  
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  readPulsesFromEEPROM();
  
  // Set button interrupt
  attachInterrupt(digitalPinToInterrupt(BTN_PIN), buttonPressed, FALLING);
  
  // Set pulse input interrupts
  PCICR |= B00000100; // P1 and P2 (port D)
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
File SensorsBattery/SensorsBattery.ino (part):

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#define MODE_NTC        4

#define LED_PIN         8
#define NTC_ENABLE_PIN  0
#define NTC_PIN         A2
#define BTN_PIN         3
#define JMP_PIN         9

#define PAYLOAD_LEN     11
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
SI7021 sensorSI7021; // SI7021 instance
BME280 sensorBME280; // BME280 instance
NTCSensor sensorNTC(NTC_ENABLE_PIN, NTC_PIN); // NTC instance

// Payload buffer
// Header | Battery_MSB | Battery_LSB | TransmitPower | TransmitInterval | Sensor1_MSB | Sensor1_LSB | Sensor2_MSB | Sensor2_LSB | Sensor3_MSB | Sensor3_LSB
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  pinMode(LED_PIN, OUTPUT);
  
  // Button
  pinMode(BTN_PIN, INPUT_PULLUP);
  
  // Jumper J1
  pinMode(JMP_PIN, INPUT_PULLUP);
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  delay(10);
  
  // Enter programming mode (currently does nothing) if button is pressed. Also set debug mode.
  if (!digitalRead(BTN_PIN)) {
    enterProgMode();
    isDebugMode = true;
  }
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  #endif

  // Set button interrupt
  attachInterrupt(digitalPinToInterrupt(BTN_PIN), wakeUpFromBtn, FALLING);
  
  // Set force send so that message is sent after startup and led blinked
  forceSend = true;
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
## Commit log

2019-12-26 Initial release
2019-12-29 Fix NTC enable pin bug
    Do not change any pinmodes or values if enablePin is not in use when reading temperature.
2019-12-29 Add version history
2019-12-29 Fix NTCSensor enable pin bug (#1)
    * Fix NTC enable pin bug
    Do not change any pinmodes or values if enablePin is not in use when reading temperature.
    * Add version history
    * Update README.md
2020-01-27 Fix overflow bug in gateway uptime
2020-02-03 Fix overflow bug in gateway uptime calculation
2020-02-03 Add image of wired Si7021 breakout board for outdoor sensor use
2020-02-04 Bump minor version to 3
2020-02-04 Add v1.0.2 history
2020-02-09 Add node importancy functionality
2020-02-09 Add last received node id functionality
2020-02-09 Fix importancy header bit set
2020-02-10 Add last received register, update headers
2020-02-14 Refine summary
2020-02-15 Refine terminals and buttons part
2020-02-15 Adjust delay for clearing EEPROM
2020-02-15 Disable external interrupt by default
2020-02-15 Add interrupt pin to gateway
    Adds:
    * External interrupt to gateway.
    * ID of the last received node to gateway Modbus registers.
    * Importance setting to battery/pulse nodes.
    Refines and updates readme with regards to previous points. Also has some general cleaning and clarification of readme.
2020-02-15 Add version 1.1.0 info
2020-03-15 Fix possible division by zero error
2020-03-15 Fix possible problem with memory allocation
2020-03-21 Refine sensor reading and calculations
2020-03-21 Bump copyright years to 2020
2020-03-21 Update GPL to v3
2020-03-21 Update version history
2020-03-31 Get rid of float calculation
2020-03-31 Update version date
2020-04-09 Initial commit of RFM69HW support
2020-04-16 Remove redundant instructions
2020-04-23 Fix transaction handling
    Use beginTransaction() and endTransaction() to prevent interrupts corrupting data. Also use transfer() instead of transfer16() to write register address. Closes #8
2020-06-07 Fix transmit powers
2020-06-07 Update README, add image of water temperature node
2020-09-07 Fix #12
2020-09-07 Update readme, bump gateway version
2020-10-13 Initial version
2020-10-14 Add check for broadcasts
2020-10-16 Fixes, initial working version
2021-01-09 Not implementing yet send and forget mode
2021-01-09 Update/add example scripts
2021-02-01 Add ability to set IDs without headers
2021-02-01 Update topology for new footprints

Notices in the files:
SensorsBattery/SensorsBattery.ino:
Copyright (c) 2020 aattww (https://github.com/aattww/)
This program is free software: you can redistribute it and/or modify
it under the terms of the GNU General Public License as published by
the Free Software Foundation, either version 3 of the License, or
(at your option) any later version.
parts and their libraries:
SparkFun-LED: Licensing: Creative Commons ShareAlike 4.0 International - https://creativecommons.org/licenses/by-sa/4.0
micrel: Copyright (C) 2008, Bob Starr
